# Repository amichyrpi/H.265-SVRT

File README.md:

# H.265 SVRT

This is a **work in progress**. SteamVR driver and Raspberry Pi 4 receiver. This project is in development and is not stable, consider it as **alpha**.

## TODO

- [ ] Create the SVRT Utility App
  - [ ] Framerate and latency measurements
  - [x] Framerate changer with 60 Hz and 30 Hz presets
  - [ ] SteamVr driver installer with sync with latest version and automatic updates
  - [ ] Usage time measurements
  - [ ] Longest session time measurements
  - [ ] Start steamvr button that load the driver in steamvr otherwise it will not be loaded
  - [ ] Tracking support to pair a vive tracker to the headset
  - [ ] SVRT Firmware updater

## Usage/Installing

Builds and driver are available on the [Releases](https://github.com/amichyrpi/H.265-SVRT/releases) page.

### Compiling on Raspberry Pi

Before compilling H.265 SVRT you need to be running a 64-bit Raspberry Pi OS image with KMS enabled and FFmpeg. If you don't have a 64-bit Raspberry Pi OS image, you can install it by using [Raspberry Pi Imager](https://www.raspberrypi.com/software/). You can enable KMS and install FFmpeg using the following commands:

- **KMS**
  ```sh
  config=/boot/firmware/config.txt
  test -f "$config" || config=/boot/config.txt
  grep -qxF 'dtoverlay=vc4-kms-v3d' "$config" || \
    echo 'dtoverlay=vc4-kms-v3d' | sudo tee -a "$config"
  sudo reboot
  ```

- **FFmpeg**
  ```sh
  sudo apt update
  sudo apt install -y ffmpeg
  ffmpeg -hide_banner -decoders 2>&1 | grep hevc_v4l2request
  ```

- **Disable Wi-Fi power saving**

  Wi-Fi power saving can introduce periodic latency spikes, bitrate stalls,
  and dropped stream frames. Disable it persistently for the active `wlan0`
  NetworkManager connection, then reboot to apply the radio setting:

  ```sh
  wifi_connection="$(nmcli -g GENERAL.CONNECTION device show wlan0)"
  sudo nmcli connection modify "$wifi_connection" 802-11-wireless.powersave 2
  sudo reboot
  ```

  After reconnecting, verify that the profile reports the raw value `2`:

  ```sh
  wifi_connection="$(nmcli -g GENERAL.CONNECTION device show wlan0)"
  nmcli -g 802-11-wireless.powersave connection show "$wifi_connection"
  ```

- **Lock the Pi 4 core clock for high-rate KMS output**

  Lock the core clock at its normal 500 MHz performance value to avoid a
  display clock transition while high-rate video is being scanned out:

  ```sh
  config=/boot/firmware/config.txt
  test -f "$config" || config=/boot/config.txt
  grep -qxF 'force_turbo=1' "$config" || echo 'force_turbo=1' | sudo tee -a "$config"
  grep -qxF 'core_freq_min=500' "$config" || echo 'core_freq_min=500' | sudo tee -a "$config"
  sudo reboot
  ```

  This increases idle power use and heat. Verify adequate cooling and power
  after reboot:

  ```sh
  vcgencmd measure_clock core
  vcgencmd measure_temp
  vcgencmd get_throttled
  ```

H.265 SVRT requires the following libraries to be installed:

- **Before dependencies installation**
  ```sh
  sudo apt update
  sudo apt full-upgrade -y
  ```

- **Dependencies installation**
  ```sh
  sudo apt install -y build-essential cmake git ninja-build pkg-config \
    libsdl2-dev libavformat-dev libavcodec-dev libavutil-dev libdrm-dev \
    libegl1-mesa-dev libgles2-mesa-dev libgbm-dev libudev-dev libasound2-dev
  ```

The build process is otherwise normal for a CMake program:

```sh
git clone https://github.com/amichyrpi/H.265-SVRT.git
cd H.265-SVRT
mkdir build && cd build
cmake .. -G Ninja -DSVRT_BUILD_DRIVER=OFF \
  -DSVRT_BUILD_VENDORED_SDL=ON \
  -DCMAKE_BUILD_TYPE=Release
cmake --build . --parallel
ctest --output-on-failure
```

Optionally, to install the program:

```sh
sudo useradd --system --no-create-home --shell /usr/sbin/nologin svrt-receiver
sudo usermod -aG video,render svrt-receiver
sudo cmake --install .
sudo systemctl daemon-reload
sudo systemctl enable --now svrt-receiver.service
```

The service runs as the `svrt-receiver` user with membership in the `video` and `render` groups, which grants access to the DRM devices for `SDL_VIDEODRIVER=kmsdrm` without root.

### SteamVR driver setup

You can easily install the driver by using the SVRT Utility App on both Windows and Linux, you can find the app in the [Releases](https://github.com/amichyrpi/H.265-SVRT/releases) page.

You can also build and install the driver manually by using the following commands:

- **Windows**
  ```powershell
  git clone https://github.com/amichyrpi/H.265-SVRT.git
  Set-Location H.265-SVRT
  cmake -S . -B build -A x64 `
    -DSVRT_BUILD_PI_LIBRARY=OFF `
    -DSVRT_BUILD_RECEIVER=OFF `
    -DSVRT_BUILD_TESTS=OFF
  cmake --build build --config Release --parallel
  $vrpathreg = Join-Path ${env:ProgramFiles(x86)} `
    'Steam\steamapps\common\SteamVR\bin\win64\vrpathreg.exe'
  & $vrpathreg adddriver (Resolve-Path 'build\svrt')
  ```

### Starting order

The Raspberry Pi receiver is started at Raspberry Pi boot, and the SteamVR driver is started at SteamVR boot. The driver automatically detects when the Raspberry Pi receiver becomes available.

### Stereo resolution and transport

The headset renders `1440x1600` per eye and packs both eyes side by side in one
`2880x1600` HEVC stream. The Raspberry Pi decodes that stream with the single
`rpivid` H.265 hardware decoder and presents its DRM PRIME frames directly with
KMS. The selectable refresh rates are 60 Hz and 30 Hz, with 60 Hz as the
default. Runtime discovery uses mDNS/DNS-SD (`_stearlight._tcp.local`) with a
UDP discovery fallback. TCP 9945 carries session/configuration and clock-sync
messages; video uses 1200-byte UDP datagrams on 9944 with 10+2 Reed-Solomon
FEC and bounded frame reassembly. Tracking returns over UDP 9947 at 250 Hz,
and audio uses UDP 9946. SSH is only a development/deployment tool.

To start the installed Raspberry Pi receiver manually:

```sh
sudo systemctl start svrt-receiver.service
```

To run it directly without the systemd service:

```sh
sudo systemctl stop svrt-receiver.service
cd ~/H.265-SVRT/build
sudo env SDL_VIDEODRIVER=kmsdrm ./pi-receiver/svrt-receiver 9944
```

To run at boot without a connected HDMI display:

```sh
sudo systemctl edit svrt-receiver.service
```

Enter the following override, save it, and restart the service:

```ini
[Service]
ExecStart=
ExecStart=/usr/local/bin/svrt-receiver --headless 9944
```

```sh
sudo systemctl daemon-reload
sudo systemctl restart svrt-receiver.service
```

## Testing stream latency

Stop SteamVR before running the latency tester so it can use the Raspberry Pi video connection.

- **Windows**
  ```powershell
  py -m pip install av
  py scripts\stream-latency-test.py ROOT.local --frames 30
  ```

- **Linux**
  ```sh
  python3 -m pip install --user av
  python3 scripts/stream-latency-test.py ROOT.local --frames 30
  ```

## License

This project is licensed under the Functional Source License, Version 1.1,
with Apache License 2.0 as the Future License (`FSL-1.1-ALv2`). See the
[LICENSE](LICENSE) file for details.

This project uses parts of the [Vanilla](https://github.com/vanilla-wiiu/vanilla) code, to handle the DRM scanout and the KMS overlay plane. The Vanilla code is licensed under the GPL-2.0 License. See the [LICENSE](https://github.com/vanilla-wiiu/vanilla/blob/master/LICENSE) file for details.

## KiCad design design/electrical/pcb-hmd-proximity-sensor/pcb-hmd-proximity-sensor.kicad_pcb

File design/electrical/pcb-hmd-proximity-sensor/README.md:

# Stearlight HMD proximity sensor

This project is the small face-proximity daughterboard for the HMD. It places a Vishay `VCNL36825T` at one board edge and a five-circuit JST SUR side-entry connector at the opposite edge.

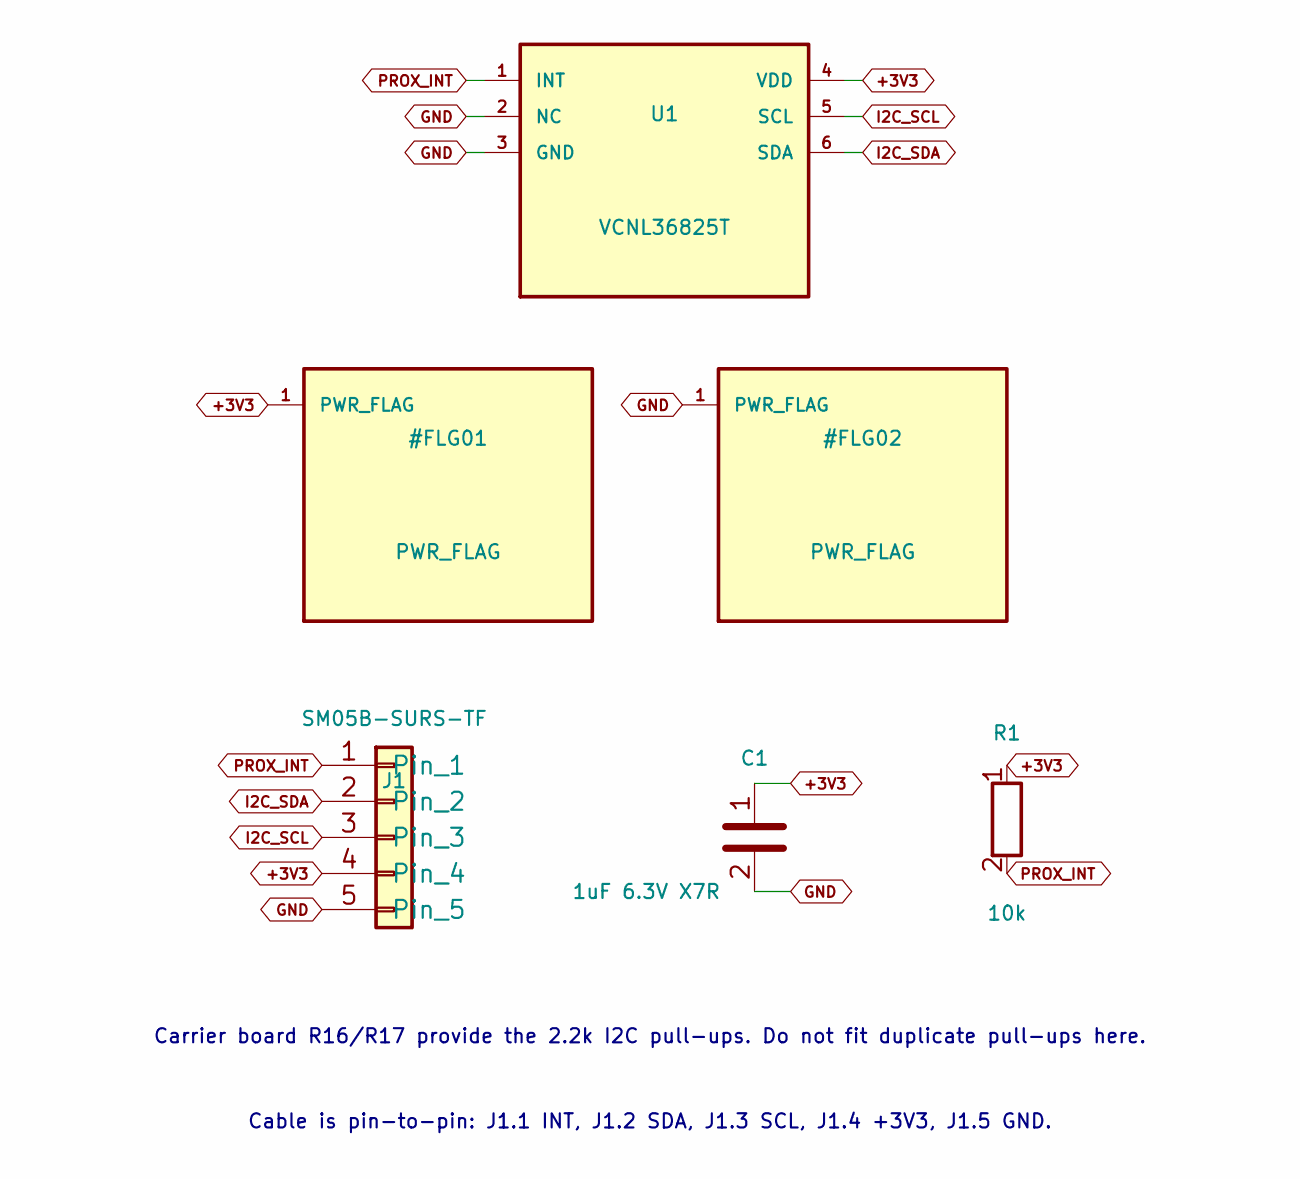
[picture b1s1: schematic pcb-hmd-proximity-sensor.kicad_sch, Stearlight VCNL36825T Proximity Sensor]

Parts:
C1: 1uF 6.3V X7R; C_0402_1005Metric
J1: SM05B-SURS-TF; JST_SUR_SM05B-SURS-TF_1x05-1MP_P0.80mm_Horizontal
R1: 10k; R_0402_1005Metric
U1: VCNL36825T

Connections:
+3V3: C1.1, J1.4, R1.1, U1.4 (VDD)
GND: C1.2, J1.5, U1.2 (NC), U1.3 (GND)
I2C_SCL: J1.3, U1.5 (SCL)
I2C_SDA: J1.2, U1.6 (SDA)
PROX_INT: J1.1, R1.2, U1.1 (INT)

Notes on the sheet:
Carrier board R16/R17 provide the 2.2k I2C pull-ups. Do not fit duplicate pull-ups here.
Cable is pin-to-pin: J1.1 INT, J1.2 SDA, J1.3 SCL, J1.4 +3V3, J1.5 GND.

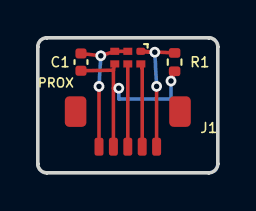
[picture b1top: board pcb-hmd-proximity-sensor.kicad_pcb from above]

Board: 2 copper layers, 10.0 x 7.5 mm, 4 parts (0 on the bottom side), 5 nets.

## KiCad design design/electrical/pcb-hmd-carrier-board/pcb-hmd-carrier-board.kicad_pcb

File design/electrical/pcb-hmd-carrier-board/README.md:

# Stearlight HMD carrier - Rev A

This directory contains the first engineering milestone for the CM4-based Stearlight
VR HMD carrier. The project is a real hierarchical KiCad design with a six-layer,
145.70 mm x 49.82 mm placement board. It is deliberately marked **not for fabrication**
until the unresolved product interfaces and high-speed layout gates below are closed.

## Current milestone

- Eight Board2-specific hierarchical sheets recover CM4, power, PCIe/USB 3,
  audio, display, interfaces, microSD and supporting circuitry from the approved PCB.
- The official Raspberry Pi CM4 200-pin connector definition and combined carrier
  footprint are reused from `cm4-io/`.
- The schematic passes KiCad ERC with zero errors and one documented warning for
  the externally reserved single-ended `BAT_ID` net.
- The current board2 PCB contains 312 footprints on a six-layer construction.
- The 145.70 x 49.82 mm outline and required placement changes were formally
  approved on 2026-08-15; the future shell must use this frozen PCB envelope.
- Placement follows the supplied drawing: charge USB-C and jack on the left, two
  forward microphones, USB-C host and battery on the right, CM4 centered on the
  rear, and the 100-pin tracking connector on the rear-left region.
- The additive `pcb-hmd-carrier-board2.kicad_pcb` variant now carries the complete
  dual-eye BOE display placement: exact 50-pin panel connectors, two HDMI-to-dual-
  DSI bridges, clocks, power, bias, backlight, controls, passives and test pads.
  The existing manually placed carrier components were not moved.
- The useful legacy rear-side power, charge, service and tracking blocks have now
  been ported to the new outline. The obsolete source-board copy was removed.
- The complete native microSD circuit is restored on the main PCB. CM4 Lite is the
  primary fitted Rev A assembly; the optional eMMC assembly marks that block DNP.
- The JLCPCB `JLC06161H-3313` six-layer stack, two continuous internal GND planes,
  production net classes and narrowly scoped exact-footprint DRC rules are encoded.

Open [pcb-hmd-carrier-board2.kicad_pro](pcb-hmd-carrier-board2.kicad_pro) in KiCad 10
for the restored carrier and its matching Board2 schematic hierarchy. The original
project remains a reference baseline.

## Architecture

```text
protected 2S pack <-> BQ25798 charger/power path <- TPS25751D <- charge USB-C
        |
        +-> TPS568230 5 V / 8 A -> CM4 + protected USB host VBUS
        +-> CM4 3.3 V output -> control/audio rails
                               -> TPS62825 1.05 V USB controller rail

CM4 PCIe Gen2 x1 -> UPD720202 -> HD3SS3212 -> USB-C SuperSpeed host
CM4 PCM/I2S      -> TLV320AIC3204 -> TRRS + two IM73A135 microphones
```

## Review outputs

- `output/docs/Stearlight_HMD_Carrier_RevA_Schematic.pdf`
- `output/review/carrier-top-corrected.png`
- `output/review/carrier-bottom-corrected.png`
- `docs/BOM.csv`
- `output/assembly/PickAndPlace.csv`
- `output/reports/ERC.rpt`
- `output/reports/DRC.rpt`
- `output/review/legacy-port/carrier2-bottom-final.png`
- `output/review/legacy-port/carrier2-top-final.png`
- `output/reports/DRC-pcb-hmd-carrier-board2-legacy-port.rpt`
- `output/reports/DRC-pcb-hmd-carrier-board2-production-current.rpt`
- `output/reports/ERC-pcb-hmd-carrier-board-current.rpt`
- `output/production-audit/`
- `output/review/production-current/carrier2-top.png`
- `output/review/production-current/carrier2-bottom.png`
- `output/review/production-current/pcb-hmd-carrier-board2-review.step`

The authoritative PCB is electrically netted and routing is being developed in
isolated, measured candidates before copper is promoted. Its current geometry DRC
has zero violations and zero known shorts; the baseline still has 499 unconnected
groups and 14 of 278 named nets contain copper. All 312 PCB references are present
in the recovered hierarchy with zero KiCad schematic-parity issues. Gerbers are not
generated until the routed release candidate passes every release check; this keeps
a placement/routing experiment from being mistaken for fabrication data.

## Mandatory fabrication/production gates

1. Obtain the complete controlled BOE initialization/timing specification and
   validate the NT57860 sequence, DSI split and 1440 x 1600 timing on hardware.
2. Define the Lighthouse tracking-board pinout for `J7`.
3. Review every UPD720202 strap, reset, sequencing and passive against the gated
   Renesas hardware manual/reference schematic.
4. Obtain JLCPCB review/tuning of the preliminary HDMI/MIPI, PCIe, USB3 and USB2
   differential geometries against the selected `JLC06161H-3313` stack and coupons.
5. Recheck the exact JAE USB-C and Same Sky jack land patterns against the enclosure
   datum before freezing the shell; their real connector bodies are present in the
   current 3D review.
6. Confirm the protected 2S battery pack, connector/harness ratings, NTC curve,
   pack ID policy and independent BMS certification.
7. Configure and validate the TPS25751 PD image/PDOs and charger limits.
8. Freeze shell CAD, CM4 heatsink/fan clearance, acoustic ducts and mounting datum.
9. Replace recovered passive/`VERIFY` pin types with controlled vendor symbols as
   restricted datasheets become available; reference and pad/net reconciliation is complete.

See `docs/DESIGN_PLAN.md`, `docs/POWER_BUDGET.md`, `docs/INTERFACES.md`,
`docs/STACKUP.md` and `docs/SOURCES.md` for the engineering assumptions.
The ordered routing, power-sequencing, DFM and bring-up workflow is in
`docs/PRODUCTION_EXECUTION_PLAN.md`; microSD variant rules are in
`docs/CM4_LITE_MICROSD.md`.
The remaining release inputs are tracked in `docs/PRODUCTION_BLOCKERS.md`; current
review-only BOM, placement and net reports are under `output/production-audit/`.
The exact-model coverage and unresolved CAD imports are listed in
`docs/3D_MODEL_STATUS.md`; measured validation status is in `docs/VALIDATION.md`.

## Regeneration and checks

Run from this directory in PowerShell:

```powershell
./tools/validate_board2_production.ps1
```

The older reference-hierarchy regeneration path remains:

```powershell
./tools/fetch_kicad_models.ps1
python tools/generate_carrier_schematic.py
kicad-cli sch upgrade --force pcb-hmd-carrier-board.kicad_sch
Get-ChildItem sheets -Filter *.kicad_sch | ForEach-Object {
    kicad-cli sch upgrade --force $_.FullName
}
kicad-cli sch erc pcb-hmd-carrier-board.kicad_sch -o output/reports/ERC.rpt
kicad-cli sch export netlist pcb-hmd-carrier-board.kicad_sch `
    --format kicadxml -o output/pcb-hmd-carrier-board.net.xml
& "C:\Program Files\KiCad\10.0\bin\python.exe" tools/generate_carrier_pcb.py
kicad-cli pcb drc pcb-hmd-carrier-board.kicad_pcb -o output/reports/DRC.rpt `
    --all-track-errors
```

Do not generate manufacturing Gerbers until all mandatory gates are closed and DRC
is clean.

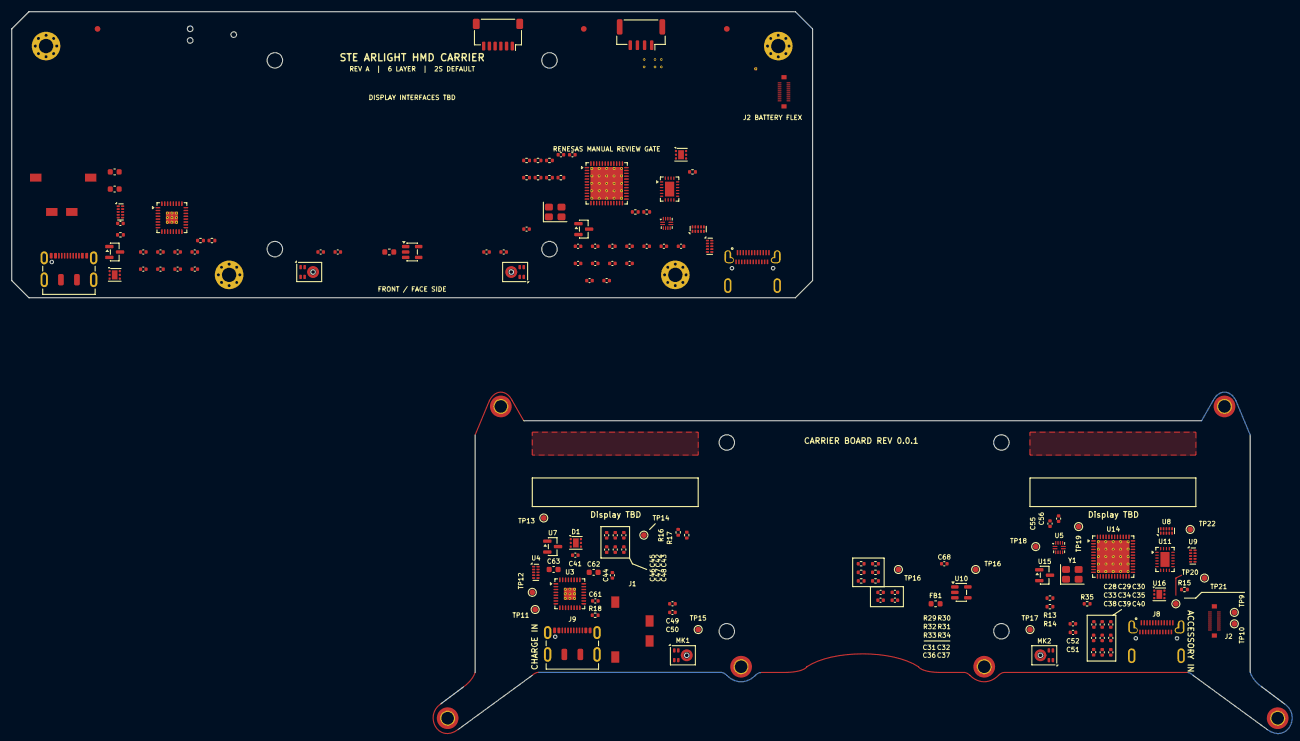
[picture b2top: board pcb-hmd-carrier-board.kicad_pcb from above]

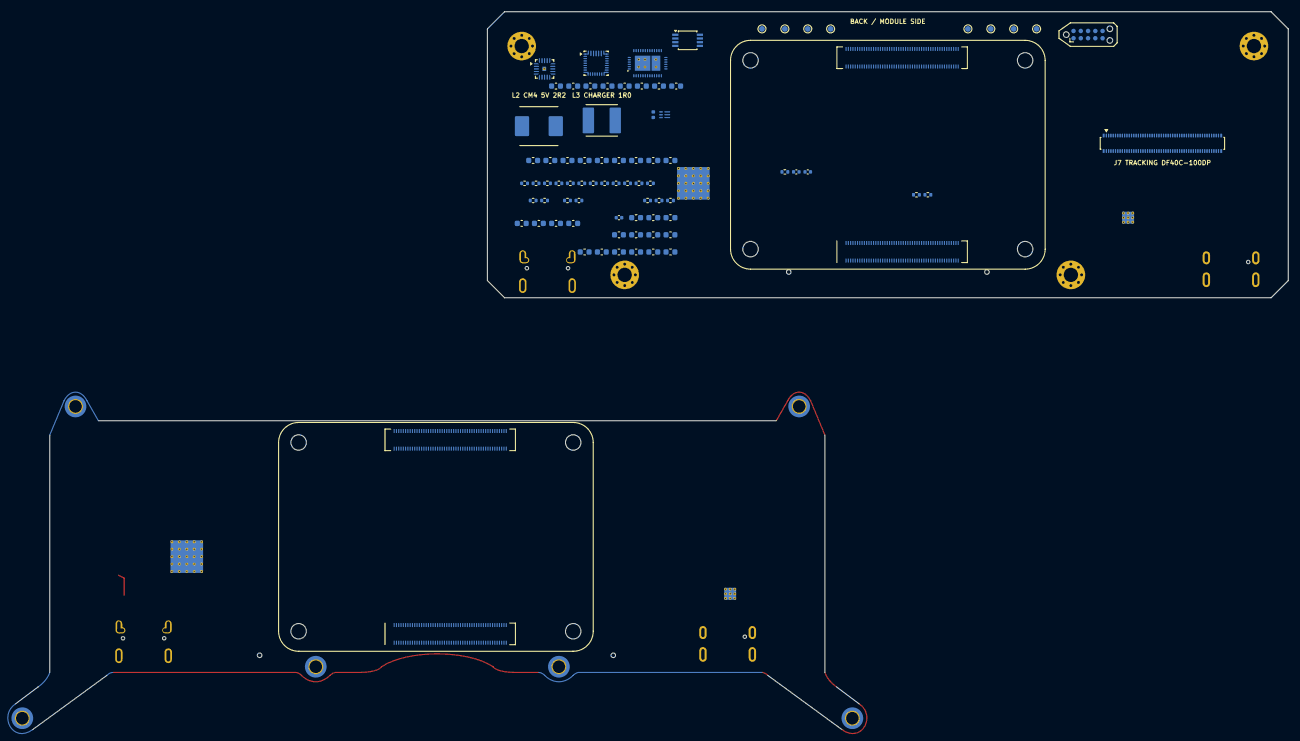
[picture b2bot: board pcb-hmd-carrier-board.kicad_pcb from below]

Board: 6 copper layers, 222.5 x 125.5 mm, 231 parts (79 on the bottom side), 120 nets, no tracks yet.

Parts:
C1, C2, C3, C4, C5, C9, C10, C11, C13, C14, C19, C20, C21, C22, C23: 10u; C_0603_1608Metric
C6, C12, C15, C24, C25: 100n; C_0603_1608Metric
C7, C8: 330p; C_0603_1608Metric
C16: 4u7; C_0603_1608Metric
C17, C18: 47n; C_0603_1608Metric
C26: 1u; C_0603_1608Metric
C27: 47p; C_0603_1608Metric
C28, C28#2, C29, C29#2, C30, C30#2, C31, C31#2, C32, C32#2, C33, C33#2, C34, C34#2, C35, C35#2, C36, C36#2, C37, C37#2, C43, C43#2, C48, C48#2: 100n; C_0402_1005Metric
C38, C38#2, C44, C44#2, C45, C45#2, C46, C46#2, C47, C47#2: 10u; C_0402_1005Metric
C39, C39#2, C40, C40#2, C41, C41#2, C42, C42#2: 1u; C_0402_1005Metric
C49, C49#2, C50, C50#2, C51, C51#2, C52, C52#2: 1u C0G; C_0402_1005Metric
C53, C54, C55, C55#2, C56, C56#2: 100n PCIe AC; C_0402_1005Metric
C57, C58: 100u low-ESR; C_0603_1608Metric
C59, C60: 22u 25V; C_0603_1608Metric
C61, C61#2: 100n JACK MIC; C_0402_1005Metric
C62, C62#2: 47u HP LEFT; C_0603_1608Metric
C63, C63#2: 47u HP RIGHT; C_0603_1608Metric
C64: 4.7u 10V; C_0603_1608Metric
C65, C66: 10u 6.3V; C_0603_1608Metric
C67: 120p C0G; C_0402_1005Metric
C68, C68#2: 100n USB3 RESET; C_0402_1005Metric
D1, D1#2: TVS2200DRVR; WSON-6-1EP_2x2mm_P0.65mm_EP1x1.6mm
FB1, FB1#2: 600R@100MHz ferrite; L_0603_1608Metric
FID1, FID2, FID3: FIDUCIAL; Fiducial_1mm_Mask2mm
H1, H2, H3, H4: M2.5; MountingHole_2.5mm_Pad_Via
J1, J1#2: SJ-43514-SMT-TR; SameSky_SJ-43514-SMT-TR
J2, J2#2: BM28 BATTERY FLEX 5A + NTC/ID; Hirose_BM28B0.6-20DS_2-0.35V
J4: 5V GND PWM TACH; JST_GH_SM04B-GHS-TB_1x04-1MP_P1.25mm_Horizontal
J5: 3V3 GND SDA SCL INT GPIO; JST_SH_SM06B-SRSS-TB_1x06-1MP_P1.00mm_Horizontal
J6: TAG-CONNECT SERVICE PADS (NO FIT); Tag-Connect_TC2050-IDC-NL_2x05_P1.27mm_Vertical
J7: DF40C-100DP-0.4V(51) TRACKING; Hirose_DF40C-100DP-0.4V_2x50-1MP_P0.4mm
J8, J8#2: DX07S024JJ2R1300 ACCESSORY; JAE_DX07S024JJ2R1300
J9, J9#2: DX07S016JA1R1500 CHARGE/SERVICE; USB_C_Receptacle_JAE_DX07S016JA1R1500
L1: 0.47uH XFL4015-471MEC; L_0402_1005Metric
L2: SRP7050TA-2R2M 2.2uH 10A; Bourns_SRP7050TA
L3: SRP5030CA-1R0M 1uH 9A; Bourns_SRP5030CA
MK1, MK1#2, MK2, MK2#2: IM73A135V01; Infineon_PG-LLGA-5-2
Module1, Module1#2: CM4 2GB/16GB/Wireless; Raspberry-Pi-4-Compute-Module
R1: 220k; R_0402_1005Metric
R2: 30k; R_0402_1005Metric
R3: 5.23k ILIM; R_0402_1005Metric
R4: 137k ILIM; R_0402_1005Metric
R5, R6: 2.2k I2C; R_0402_1005Metric
R7, R8: 10k; R_0402_1005Metric
R9: 30.1k TS; R_0402_1005Metric
R10: 10k NTC; R_0402_1005Metric
R11: 100R BATP; R_0402_1005Metric
R12: 6.04k 2S; R_0402_1005Metric
R13, R13#2, R14, R14#2: 200k; R_0402_1005Metric
R15, R15#2: ILIM 1.5A TBD; R_0402_1005Metric
R16, R16#2, R17, R17#2: I2C 2.2k; R_0402_1005Metric
R18, R18#2: MICBIAS 2.7k; R_0402_1005Metric
R19: 75k 1V05 FB; R_0402_1005Metric
R20: 100k 1V05 FB; R_0402_1005Metric
R21: 100k 1V05 PG; R_0402_1005Metric
R22: 10k WIFI EN; R_0402_1005Metric
R23: 10k BT EN; R_0402_1005Metric
R24: 75k MODE; R_0402_1005Metric
R25: 51k MODE; R_0402_1005Metric
R26: 10k CLKREQ; R_0402_1005Metric
R27: 2.2k CHG SCL; R_0402_1005Metric
R28: 2.2k CHG SDA; R_0402_1005Metric
R29, R29#2: 10k OCI PU; R_0402_1005Metric
R30, R30#2: 1.6k RREF VERIFY; R_0402_1005Metric
R31, R31#2: 10k RESET PU; R_0402_1005Metric
R32, R32#2: 10k SPI CLK PD; R_0402_1005Metric
R33, R33#2: 10k SPI CS PD; R_0402_1005Metric
R34, R34#2: 10k SPI MISO PU; R_0402_1005Metric
R35, R35#2: 10k SPI MOSI PD; R_0402_1005Metric
TP1, TP9, TP10, TP11, TP12, TP13, TP14, TP15, TP16, TP16#2, TP17, TP18, TP19, TP20, TP21, TP22: CHG_STAT; TestPoint_Pad_D1.0mm
TP2: PGOOD_5V; TestPoint_Pad_D1.0mm
TP3: BAT_ID; TestPoint_Pad_D1.0mm
TP4: +5V_SYS; TestPoint_Pad_D1.0mm
TP5: +3V3; TestPoint_Pad_D1.0mm
TP6: +1V05_USB; TestPoint_Pad_D1.0mm
TP7: GND; TestPoint_Pad_D1.0mm
TP8: VBAT_SYS; TestPoint_Pad_D1.0mm
U1: TPS62825DMQR; Texas_DMQ0006A_VSON-HR-6_1.5x1.5mm
U2: TPS568230RJER; Texas_RJE0020A_VQFN-20-1EP_3x3mm_P0.45mm_EP0.675x0.76mm_The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
U3, U3#2: TLV320AIC3204IRHBR; Texas_RHB0032M_VQFN-32-1EP_5x5mm_P0.5mm_EP2.1x2.1mm_Thermal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
U4, U4#2: TPD4E05U06DQAR; USON-10_2.5x1.0mm_P0.5mm
U5, U5#2: TUSB320LAIRWBR; Texas_X2QFN-12_1.6x1.6mm_P0.4mm
U6: BQ25798RQMR; Texas_RQM0029A_VQFN-29_4x4mm_P0.4mm
U7, U7#2: TPD2EUSB30DRTR; SOT-23
U8, U8#2, U9, U9#2: TPD4EUSB30DQAR; USON-10_2.5x1.0mm_P0.5mm
U10, U10#2: TLV75528PDBVR; SOT-23-5
U11, U11#2: HD3SS3212IRKSR; Texas_RVC0020A_WQFN-20-1EP_3x4mm_P0.5mm_EP1.6x2.6mm
U12: TPS25751DREFR; Texas_REF0038A_WQFN-38_6x4mm_DualPad
U13: CAT24C512WI-GT3; TSSOP-8_3x3mm_P0.65mm
U14, U14#2: UPD720202K8-711-BAA-A; QFN-48-1EP_7x7mm_P0.5mm_EP5.7x5.7mm_ThermalVias
U15, U15#2: TLV803EA30DBZR; SOT-23
U16, U16#2: TPS2553-1DRVR; WSON-6-1EP_2x2mm_P0.65mm_EP1x1.6mm
Y1, Y1#2: 24MHz; Crystal_SMD_3225-4Pin_3.2x2.5mm

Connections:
+1V05_USB: C28.1, C28#2.1, C29.1, C29#2.1, C30.1, C30#2.1, C31.1, C31#2.1, C32.1, C32#2.1, C33.1, C33#2.1, C39.1, C39#2.1, C65.1, C66.1, C67.1, L1.2, R19.1, TP6.1, U14.6, U14.9, U14.21, U14.30, U14.33, U14.39, U14.42, U14#2.6, U14#2.9, U14#2.21, U14#2.30, U14#2.33, U14#2.39, U14#2.42
+2V8_MIC: C42.1, C42#2.1, MK1.2, MK1#2.2, MK2.2, MK2#2.2, U10.5, U10#2.5
+3V3: C3.1, C34.1, C34#2.1, C35.1, C35#2.1, C36.1, C36#2.1, C37.1, C37#2.1, C38.1, C38#2.1, C40.1, C40#2.1, C43.1, C43#2.1, C64.1, C68.1, C68#2.1, FB1.1, FB1#2.1, J5.1, J6.1, Module1#2.78, Module1#2.84, Module1#2.86, R8.1, R13.1, R13#2.1, R14.1, R14#2.1, R16.1, R16#2.1, R17.1, R17#2.1, R21.1, R22.1, R23.1, R26.1, R29.1, R29#2.1, R31.1, R31#2.1, R34.1, R34#2.1, TP5.1, U1.1, U1.6, U3.6, U3.30, U3#2.6, U3#2.30, U5.3, U5.12, U5#2.3, U5#2.12, U11.6, U11#2.6, U12.38, U14.3, U14.12, U14.22, U14.25, U14.34, U14.43, U14#2.3, U14#2.12, U14#2.22, U14#2.25, U14#2.34, U14#2.43, U15.3, U15#2.3
+3V3_AUDIO: C41.1, C41#2.1, C45.1, C45#2.1, C48.1, C48#2.1, FB1.2, FB1#2.2, U3.26, U3#2.26, U10.1, U10.3, U10#2.1, U10#2.3
+5V_SYS: C57.1, C58.1, J4.1, L2.2, Module1#2.77, Module1#2.79, Module1#2.81, Module1#2.83, Module1#2.85, Module1#2.87, R1.1, TP4.1, U12.34, U12.35, U16.6, U16#2.6
AUDIO_1V8_LDO: C44.1, C44#2.1, U3.24, U3.29, U3#2.24, U3#2.29
AUDIO_MCLK: Module1#2.54, U3.1, U3#2.1
AUDIO_REF: C46.1, C46#2.1, U3.18, U3#2.18
AUDIO_RESET_N: Module1#2.34, U3.31, U3#2.31
BAT+: C24.1, J2.P1, R11.2, U6.22, U6.23
BATP: R11.1, U6.18
BAT_ID: J2.2, TP3.1
BST1: C17.1, U6.4
BST2: C18.1, U6.19
BST_5V: C25.1, U2.1
BT_ENABLE_N: Module1#2.91, R23.2
CC1: C7.1, J8#2.A5, J9#2.A5, U5.1, U5#2.1, U12.28
CC2: C8.1, J8#2.B5, J9#2.B5, U5.2, U5#2.2, U12.29
CHASSIS_GND: J8#2.SH, J9#2.SH
CHG_IRQ_N: R8.2, U6.21, U12.18
CHG_SCL: R27.2, U6.14, U12.17
CHG_SDA: R28.2, U6.15, U12.16
CHG_STAT: TP1.1, U6.1
CM4_EXT_RESET_N: J6.8, Module1#2.100
EMMC_BOOT_N: J6.7, Module1#2.93
FAN_PWM: J4.3, Module1#2.31
FAN_TACH: J4.4, Module1#2.30
FB_5V: C27.1, R1.2, R2.1, U2.14
GND: C1.2, C2.2, C3.2, C4.2, C5.2, C6.2, C7.2, C8.2, C9.2, C10.2, C11.2, C12.2, C13.2, C14.2, C15.2, C16.2, C19.2, C20.2, C21.2, C22.2, C23.2, C24.2, C26.2, C27.2, C28.2, C28#2.2, C29.2, C29#2.2, C30.2, C30#2.2, C31.2, C31#2.2, C32.2, C32#2.2, C33.2, C33#2.2, C34.2, C34#2.2, C35.2, C35#2.2, C36.2, C36#2.2, C37.2, C37#2.2, C38.2, C38#2.2, C39.2, C39#2.2, C40.2, C40#2.2, C41.2, C41#2.2, C42.2, C42#2.2, C43.2, C43#2.2, C44.2, C44#2.2, C45.2, C45#2.2, C46.2, C46#2.2, C47.2, C47#2.2, C48.2, C48#2.2, C57.2, C58.2, C59.2, C60.2, C64.2, C65.2, C66.2, C68.2, C68#2.2, D1.1, D1.2, D1.3, D1.7, D1#2.1, D1#2.2, D1#2.3, D1#2.7, J1#2.4, J2.P2, J4.2, J5.2, J6.2, J6.10, J8#2.A1, J8#2.A12, J8#2.B1, J8#2.B12, J9#2.A1, J9#2.A12, J9#2.B1, J9#2.B12, MK1.4, MK1.5, MK1#2.4, MK1#2.5, MK2.4, MK2.5, MK2#2.4, MK2#2.5, Module1#2.1, Module1#2.2, Module1#2.7, Module1#2.8, Module1#2.13, Module1#2.14, Module1#2.22, Module1#2.23, Module1#2.32, Module1#2.33, Module1#2.42, Module1#2.43, Module1#2.52, Module1#2.53, Module1#2.59, Module1#2.60, Module1#2.65, Module1#2.66, Module1#2.71, Module1#2.74, Module1#2.98, Module1#2.101, Module1#2.107, Module1#2.108, Module1#2.113, Module1#2.114, Module1#2.119, Module1#2.120, Module1#2.125, Module1#2.126, Module1#2.131, Module1#2.132, Module1#2.137, Module1#2.138, Module1#2.144, Module1#2.150, Module1#2.155, Module1#2.156, Module1#2.161, Module1#2.162, Module1#2.167, Module1#2.168, Module1#2.173, Module1#2.174, Module1#2.179, Module1#2.180, Module1#2.185, Module1#2.186, Module1#2.191, Module1#2.192, Module1#2.197, Module1#2.198, R2.2, R4.2, R9.2, R10.2, R12.2, R15.2, R15#2.2, R20.2, R25.2, R30.2, R30#2.2, R32.2, R32#2.2, R33.2, R33#2.2, R35.2, R35#2.2, TP7.1, U1.4, U2.7, U2.8, U2.13, U2.18, U2.21, U3.7, U3.12, U3.17, U3.28, U3#2.7, U3#2.12, U3#2.17, U3#2.28, U4.3, U4.5, U4.8, U4#2.3, U4#2.5, U4#2.8, U5.5, U5.10, U5.11, U5#2.5, U5#2.10, U5#2.11, U6.10, U6.11, U6.12, U6.13, U6.27, U7.3, U7#2.3, U8.3, U8.8, U8#2.3, U8#2.8, U9.3, U9.8, U9#2.3, U9#2.8, U10.2, U10#2.2, U11.2, U11.5, U11.11, U11.20, U11#2.2, U11#2.5, U11#2.11, U11#2.20, U12.11, U12.12, U12.14, U12.31, U12.39, U13.1, U13.2, U13.3, U13.4, U13.7, U14.27, U14.49, U14#2.27, U14#2.49, U15.1, U15#2.1, U16.5, U16.7, U16#2.5, U16#2.7, Y1.2, Y1.4, Y1#2.2, Y1#2.4
HP_L: C62.2, C62#2.2, J1#2.2, U4.1, U4#2.1
HP_L_CODEC: C62.1, C62#2.1, U3.25, U3#2.25
HP_R: C63.2, C63#2.2, J1#2.3, U4.2, U4#2.2
HP_R_CODEC: C63.1, C63#2.1, U3.27, U3#2.27
I2C_SCL: J5.4, J6.4, Module1#2.56, R16.2, R16#2.2, U3.9, U3#2.9, U5.8, U5#2.8
I2C_SDA: J5.3, J6.3, Module1#2.58, R17.2, R17#2.2, U3.10, U3#2.10, U5.7, U5#2.7
I2Ct_SCL: R6.2, U12.9, U13.6
I2Ct_SDA: R5.2, U12.8, U13.5
I2S_BCLK: Module1#2.49, U3.2, U3#2.2
I2S_DIN: Module1#2.27, U3.5, U3#2.5
I2S_DOUT: Module1#2.25, U3.4, U3#2.4
I2S_LRCLK: Module1#2.26, U3.3, U3#2.3
ILIM_HIZ: R3.2, R4.1, U6.17
JACK_MIC: C61.1, C61#2.1, J1#2.1, R18.2, R18#2.2, U4.4, U4#2.4
JACK_MIC_CODEC: C61.2, C61#2.2, U3.21, U3#2.21
LDO_1V5: C2.1, U12.2, U12.3, U12.4
LDO_3V3: C1.1, R5.1, R6.1, R7.1, R27.1, R28.1, U12.1, U13.8
MICBIAS: C47.1, C47#2.1, R18.1, R18#2.1, U3.19, U3#2.19
MIC_L_N: C50.2, C50#2.2, U3.16, U3#2.16
MIC_L_P: C49.2, C49#2.2, U3.15, U3#2.15
MIC_L_RAW_N: C50.1, C50#2.1, MK1.3, MK1#2.3
MIC_L_RAW_P: C49.1, C49#2.1, MK1.1, MK1#2.1
MIC_R_N: C52.2, C52#2.2, U3.13, U3#2.13
MIC_R_P: C51.2, C51#2.2, U3.14, U3#2.14
MIC_R_RAW_N: C52.1, C52#2.1, MK2.3, MK2#2.3
MIC_R_RAW_P: C51.1, C51#2.1, MK2.1, MK2#2.1
MODE_5V: R24.2, R25.1, U2.15
PCIE_CLKREQ_N: Module1#2.102, R26.2, U14.10, U14#2.10
PCIE_CLK_N: Module1#2.112, U14.2, U14#2.2
PCIE_CLK_P: Module1#2.110, U14.1, U14#2.1
PCIE_RST_N: Module1#2.109, U14.47, U14#2.47
PCIE_RX_N: C56.2, C56#2.2, Module1#2.118
PCIE_RX_P: C55.2, C55#2.2, Module1#2.116
PCIE_RX_USB3_N: C56.1, C56#2.1, U14.5, U14#2.5
PCIE_RX_USB3_P: C55.1, C55#2.1, U14.4, U14#2.4
PCIE_TX_CM4_N: C54.1, Module1#2.124
PCIE_TX_CM4_P: C53.1, Module1#2.122
PCIE_TX_N: C54.2, U14.8, U14#2.8
PCIE_TX_P: C53.2, U14.7, U14#2.7
PD_IRQ_N: R7.2, U12.10
PGOOD_5V: TP2.1, U2.9
PMID: C13.1, C14.1, C15.1, U6.29
PPHV: C4.1, C5.1, C6.1, U6.2, U6.3, U6.8, U6.9, U12.20, U12.21, U12.22
PROG: R12.1, U6.20
PROX_GPIO: J5.6, Module1#2.41
PROX_INT: J5.5, Module1#2.47
REGN: C16.1, R3.1, U6.5
RUN_PG: J6.9, Module1#2.92
SPI_CLK: R32.1, R32#2.1, U14.15, U14#2.15
SPI_CS_N: R33.1, R33#2.1, U14.14, U14#2.14
SPI_MISO: R34.2, R34#2.2, U14.13, U14#2.13
SPI_MOSI: R35.1, R35#2.1, U14.16, U14#2.16
SW1: C17.2, L3.1, U6.28
SW2: C18.2, L3.2, U6.26
SW_5V: C25.2, L2.1, U2.6, U2.19, U2.20
TS: J2.1, R9.1, R10.1, U6.16
TYPEC_ATTACHED_N: R14.2, R14#2.2, U5.9, U5#2.9, U16.4, U16#2.4
TYPEC_FLIP: Module1#2.48, U11.9, U11#2.9
TYPEC_INT_N: Module1#2.46, R13.2, R13#2.2, U5.6, U5#2.6
UART_RX: J6.6, Module1#2.51
UART_TX: J6.5, Module1#2.55
USB1V05_FB: C67.2, R19.2, R20.1, U1.3
USB1V05_PG: R21.2, U1.2
USB1V05_SW: L1.1, U1.5
USB2_HOST_DM: J8#2.A7, J8#2.B7, U7.2, U7#2.2, U14.36, U14#2.36
USB2_HOST_DP: J8#2.A6, J8#2.B6, U7.1, U7#2.1, U14.35, U14#2.35
USB2_SERVICE_DM: J9#2.A7, J9#2.B7, Module1#2.103, U12.27
USB2_SERVICE_DP: J9#2.A6, J9#2.B6, Module1#2.105, U12.26
USB3_POR_N: R31.2, R31#2.2, U14.11, U14#2.11, U15.2, U15#2.2
USB3_RREF: R30.1, R30#2.1, U14.26, U14#2.26
USB3_RX_N: U11.8, U11#2.8, U14.32, U14#2.32
USB3_RX_P: U11.7, U11#2.7, U14.31, U14#2.31
USB3_TX_N: U11.4, U11#2.4, U14.29, U14#2.29
USB3_TX_P: U11.3, U11#2.3, U14.28, U14#2.28
USB3_XT1: U14.24, U14#2.24, Y1.1, Y1#2.1
USB3_XT2: U14.23, U14#2.23, Y1.3, Y1#2.3
USB_C_RX1_N: J8#2.B10, U8.5, U8#2.5, U11.16, U11#2.16
USB_C_RX1_P: J8#2.B11, U8.4, U8#2.4, U11.17, U11#2.17
USB_C_RX2_N: J8#2.A10, U9.5, U9#2.5, U11.12, U11#2.12
USB_C_RX2_P: J8#2.A11, U9.4, U9#2.4, U11.13, U11#2.13
USB_C_TX1_N: J8#2.A3, U8.2, U8#2.2, U11.18, U11#2.18
USB_C_TX1_P: J8#2.A2, U8.1, U8#2.1, U11.19, U11#2.19
USB_C_TX2_N: J8#2.B3, U9.2, U9#2.2, U11.14, U11#2.14
USB_C_TX2_P: J8#2.B2, U9.1, U9#2.1, U11.15, U11#2.15
USB_ILIM: R15.1, R15#2.1, U16.2, U16#2.2
USB_OC_N: R29.2, R29#2.2, U14.19, U14#2.19, U16.3, U16#2.3
VBAT_SYS: C19.1, C20.1, C21.1, C22.1, C23.1, C59.1, C60.1, TP8.1, U2.2, U2.3, U2.4, U2.5, U2.12, U6.25
VBUS_CHARGE: C9.1, C10.1, C11.1, C12.1, D1.4, D1.5, D1.6, D1#2.4, D1#2.5, D1#2.6, J9#2.A4, J9#2.A9, J9#2.B4, J9#2.B9, U12.23, U12.24, U12.25, U12.32, U12.33
VBUS_USB_HOST: J8#2.A4, J8#2.A9, J8#2.B4, J8#2.B9, U16.1, U16#2.1
VCC_5V: C26.1, R24.1, U2.17
WIFI_ENABLE_N: Module1#2.89, R22.2

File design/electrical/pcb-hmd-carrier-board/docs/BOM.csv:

"Reference","Value","Footprint","Quantity"
"C1-C3,C65,C66","10u 6.3V","Capacitor_SMD:C_0603_1608Metric","5"
"C4,C5,C9-C11,C13,C14,C20-C24","10u 25V","Capacitor_SMD:C_0603_1608Metric","12"
"C6,C12,C15,C19,C25","100n 25V","Capacitor_SMD:C_0402_1005Metric","5"
"C7,C8","330p","Capacitor_SMD:C_0402_1005Metric","2"
"C16","4.7u 10V","Capacitor_SMD:C_0402_1005Metric","1"
"C17,C18","47n 25V","Capacitor_SMD:C_0402_1005Metric","2"
"C26","1u 10V","Capacitor_SMD:C_0402_1005Metric","1"
"C27","47p","Capacitor_SMD:C_0402_1005Metric","1"
"C28-C37,C43,C48,C61,C68","100n","Capacitor_SMD:C_0402_1005Metric","14"
"C38,C44-C47","10u","Capacitor_SMD:C_0603_1608Metric","5"
"C39-C42","1u","Capacitor_SMD:C_0402_1005Metric","4"
"C49-C52","1u film/C0G","Capacitor_SMD:C_0603_1608Metric","4"
"C53-C56","100n PCIe AC","Capacitor_SMD:C_0402_1005Metric","4"
"C57,C58","100u 10V low-ESR","Capacitor_SMD:C_0402_1005Metric","2"
"C59,C60","22u 25V","Capacitor_SMD:C_0603_1608Metric","2"
"C62,C63","47u low-ESR","Capacitor_SMD:C_0402_1005Metric","2"
"C64","4.7u 10V","Capacitor_SMD:C_0603_1608Metric","1"
"C67","120p C0G","Capacitor_SMD:C_0402_1005Metric","1"
"D1","TVS2200DRVR","Package_SON:WSON-6-1EP_2x2mm_P0.65mm_EP1x1.6mm","1"
"FB1","600R@100MHz ferrite","Inductor_SMD:L_0603_1608Metric","1"
"J1","SJ-43514-SMT-TR","Stearlight:SameSky_SJ-43514-SMT-TR","1"
"J2","BM28 BATTERY FLEX 5A + NTC/ID","Stearlight:Hirose_BM28B0.6-20DS_2-0.35V","1"
"J4","5V GND PWM TACH","Connector_JST:JST_GH_SM04B-GHS-TB_1x04-1MP_P1.25mm_Horizontal","1"
"J5","PROXIMITY FLEX","Connector_JST:JST_SH_SM06B-SRSS-TB_1x06-1MP_P1.00mm_Horizontal","1"
"J7","DF40C-100DP-0.4V(51) TRACKING","Connector_Hirose_DF40:Hirose_DF40C-100DP-0.4V_2x50-1MP_P0.4mm","1"
"J8","DX07S024JJ2R1300 ACCESSORY","Stearlight:JAE_DX07S024JJ2R1300","1"
"J9","DX07S016JA1R1500 CHARGE/SERVICE","Connector_USB:USB_C_Receptacle_JAE_DX07S016JA1R1500","1"
"L1","0.47uH XFL4015-471MEC","Inductor_SMD:L_0402_1005Metric","1"
"L2","SRP7050TA-2R2M 2.2uH 10A","Stearlight:Bourns_SRP7050TA","1"
"L3","SRP5030CA-1R0M 1uH 9A","Stearlight:Bourns_SRP5030CA","1"
"MK1,MK2","IM73A135V01","Sensor_Audio:Infineon_PG-LLGA-5-2","2"
"Module1","CM4 2GB/16GB/Wireless","CM4IO:Raspberry-Pi-4-Compute-Module","1"
"R1","220k 1%","Resistor_SMD:R_0402_1005Metric","1"
"R2","30k 1%","Resistor_SMD:R_0402_1005Metric","1"
"R3","5.23k 1%","Resistor_SMD:R_0402_1005Metric","1"
"R4","137k 1%","Resistor_SMD:R_0402_1005Metric","1"
"R5,R6,R16,R17,R27,R28","2.2k","Resistor_SMD:R_0402_1005Metric","6"
"R7,R8,R22,R23,R32-R35","10k","Resistor_SMD:R_0402_1005Metric","8"
"R9","30.1k 1%","Resistor_SMD:R_0402_1005Metric","1"
"R10","10k NTC option","Resistor_SMD:R_0402_1005Metric","1"
"R11","100R 1%","Resistor_SMD:R_0402_1005Metric","1"
"R12","6.04k 1% (2S)","Resistor_SMD:R_0402_1005Metric","1"
"R13,R14","200k","Resistor_SMD:R_0402_1005Metric","2"
"R15","20k 1% (1.5A limit)","Resistor_SMD:R_0402_1005Metric","1"
"R18","2.7k","Resistor_SMD:R_0402_1005Metric","1"
"R19","75k 1%","Resistor_SMD:R_0402_1005Metric","1"
"R20","100k 1%","Resistor_SMD:R_0402_1005Metric","1"
"R21","100k","Resistor_SMD:R_0402_1005Metric","1"
"R24","75k 1% (FCCM 800kHz)","Resistor_SMD:R_0402_1005Metric","1"
"R25","51k 1% (FCCM 800kHz)","Resistor_SMD:R_0402_1005Metric","1"
"R26","10k PCIe CLKREQ pull-up","Resistor_SMD:R_0402_1005Metric","1"
"R29","10k OCI pull-up","Resistor_SMD:R_0402_1005Metric","1"
"R30","1.6k RREF - verify gated Renesas manual","Resistor_SMD:R_0402_1005Metric","1"
"R31","10k reset pull-up","Resistor_SMD:R_0402_1005Metric","1"
"TP1","CHG_STAT","TestPoint:TestPoint_Pad_D1.0mm","1"
"TP2","PGOOD_5V","TestPoint:TestPoint_Pad_D1.0mm","1"
"TP3","BAT_ID","TestPoint:TestPoint_Pad_D1.0mm","1"
"TP4","+5V_SYS","TestPoint:TestPoint_Pad_D1.0mm","1"
"TP5","+3V3","TestPoint:TestPoint_Pad_D1.0mm","1"
"TP6","+1V05_USB","TestPoint:TestPoint_Pad_D1.0mm","1"
"TP7","GND","TestPoint:TestPoint_Pad_D1.0mm","1"
"TP8","VBAT_SYS","TestPoint:TestPoint_Pad_D1.0mm","1"
"U1","TPS62825DMQR","Stearlight:Texas_DMQ0006A_VSON-HR-6_1.5x1.5mm","1"
"U2","TPS568230RJER","Package_DFN_QFN:Texas_RJE0020A_VQFN-20-1EP_3x3mm_P0.45mm_EP0.675x0.76mm_ThermalVias","1"
"U3","TLV320AIC3204IRHBR","Package_DFN_QFN:Texas_RHB0032M_VQFN-32-1EP_5x5mm_P0.5mm_EP2.1x2.1mm_ThermalVias","1"
"U4","TPD4E05U06DQAR","Package_SON:USON-10_2.5x1.0mm_P0.5mm","1"
"U5","TUSB320LAIRWBR","Package_DFN_QFN:Texas_X2QFN-12_1.6x1.6mm_P0.4mm","1"
"U6","BQ25798RQMR","Package_DFN_QFN:Texas_RQM0029A_VQFN-29_4x4mm_P0.4mm","1"
"U7","TPD2EUSB30DRTR","Package_TO_SOT_SMD:SOT-23","1"
"U8,U9","TPD4EUSB30DQAR","Package_SON:USON-10_2.5x1.0mm_P0.5mm","2"
"U10","TLV75528PDBVR","Package_TO_SOT_SMD:SOT-23-5","1"
"U11","HD3SS3212IRKSR","Package_DFN_QFN:Texas_RVC0020A_WQFN-20-1EP_3x4mm_P0.5mm_EP1.6x2.6mm","1"
"U12","TPS25751DREFR","Stearlight:Texas_REF0038A_WQFN-38_6x4mm_DualPad","1"
"U13","CAT24C512WI-GT3","Package_SO:TSSOP-8_3x3mm_P0.65mm","1"
"U14","UPD720202K8-711-BAA-A","Package_DFN_QFN:QFN-48-1EP_7x7mm_P0.5mm_EP5.7x5.7mm_ThermalVias","1"
"U15","TLV803EA30DBZR","Package_TO_SOT_SMD:SOT-23","1"
"U16","TPS2553-1DRVR","Package_SON:WSON-6-1EP_2x2mm_P0.65mm_EP1x1.6mm","1"
"Y1","24MHz 12pF","Crystal:Crystal_SMD_3225-4Pin_3.2x2.5mm","1"
"J11","BM28B0.6-20DS/2-0.35V(51) BUTTON FLEX","Stearlight:Hirose_BM28B0.6-20DS_2-0.35V_BUTTONS","1"
"D11","TJ-S3227SW1TCGLCCYRGB-A5 C601674","Stearlight:TOGIALED_TJ-S3227SW1TCGLCCYRGB-A5","1"
"R73,R76-R78","1k","Resistor_SMD:R_0402_1005Metric","4"
"R74,R75","330R","Resistor_SMD:R_0402_1005Metric","2"

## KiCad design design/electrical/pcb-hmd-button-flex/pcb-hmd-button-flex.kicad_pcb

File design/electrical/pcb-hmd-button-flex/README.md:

# Stearlight HMD front panel button flex

This project implements the headset side-button flex requested for Stearlight.The enclosure-facing side carries three vertically aligned, normally-open buttons:

1. `SW1` — volume up (`+`)
2. `SW2` — power (`PWR`)
3. `SW3` — volume down (`-`)

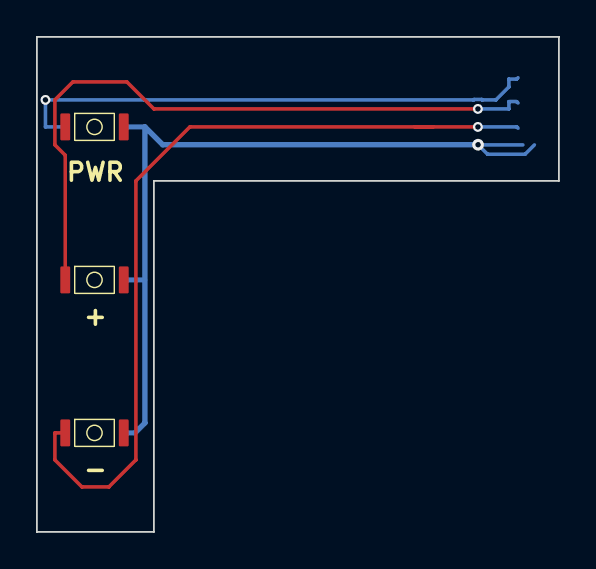
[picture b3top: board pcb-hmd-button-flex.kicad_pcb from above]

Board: 2 copper layers, 29.0 x 27.5 mm, 4 parts (1 on the bottom side), 4 nets.

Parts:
J1: BM28B0.6-20DP/2-0.35V(51); Hirose_BM28B0.6-20DP_2-0.35V
SW1: EVPAWCD4A VOL+; Panasonic_EVPAWCD4A
SW2: EVPAWCD4A POWER; Panasonic_EVPAWCD4A
SW3: EVPAWCD4A VOL-; Panasonic_EVPAWCD4A

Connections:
GND: J1.21, SW1.2, SW2.2, SW3.2
PWR_KEY_N: J1.1, SW2.1
VOL_DOWN_N: J1.17, SW3.1
VOL_UP_N: J1.9, SW1.1

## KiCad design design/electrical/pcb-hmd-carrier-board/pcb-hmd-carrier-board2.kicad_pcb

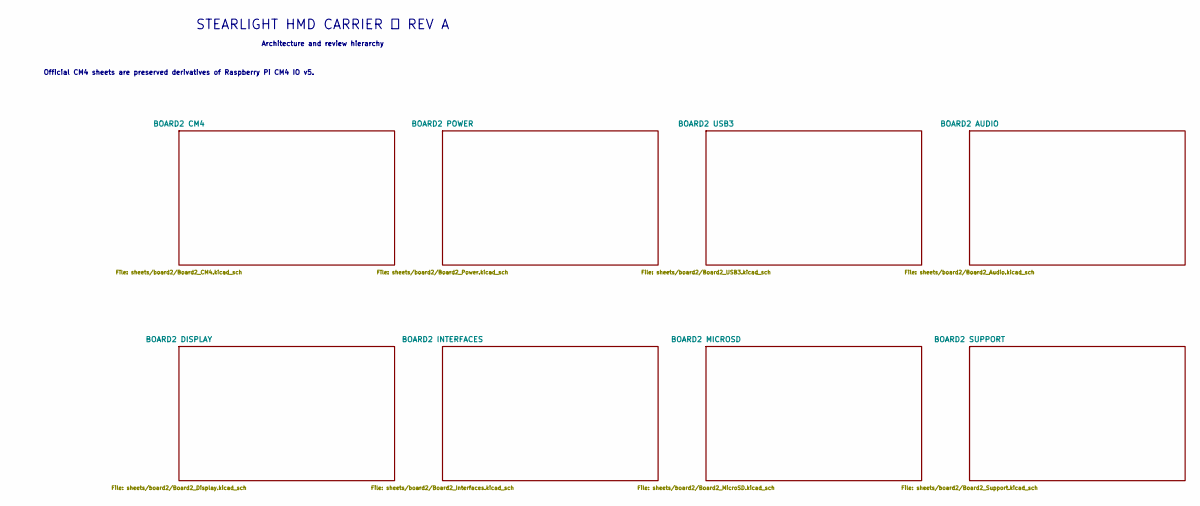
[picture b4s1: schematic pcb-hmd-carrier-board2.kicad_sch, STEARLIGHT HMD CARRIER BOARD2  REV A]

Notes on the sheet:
STEARLIGHT HMD CARRIER  REV A
Architecture and review hierarchy
Official CM4 sheets are preserved derivatives of Raspberry Pi CM4 IO v5.
